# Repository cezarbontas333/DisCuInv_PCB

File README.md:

# DisCuInv_PCB
DisCuInv is an inverter project that aims to implement a simpler power conversion strategy. The aim is to be used in solar to grid conduction, but this is only a prototype used in an educational environment to test different plant control algorithms which may be less computational intensive and less complex to implement, like PIDs or RSTs. It contains a KiCAD project, namely schematic and PCB design, that can be used to create Gerber files, BOM and CPL that can be sent to a manufacturer to create the boards. Additionally, a [proof of concept](https://github.com/cezarbontas333/DisCuInv_PID) program is provided in a separate repository that uses a PID to control the power conversion.

## Highlights
- Features integrated [half-bridge and gate drivers](https://www.infineon.com/cms/en/product/power/motor-control-ics/brushed-dc-motor-control-ics/single-half-bridge-ics/ifx007t/) that can sustain up to 40V DC inputs, but the module designed should use 24V DC.
- Control is done using Infineon's [PSoC C3M5](https://www.infineon.com/cms/en/product/microcontroller/32-bit-psoc-arm-cortex-microcontroller/32-bit-psoc-control-arm-cortex-m33-mcu/psoc-control-c3m/), a modern microcontroller with plenty of features designed for power conversion applications. Pins that are not dedicated to the specific application have been broken out to standard 2.54mm headers for additional expansion modules in testing and prototyping of bonus features.
- Has an integrated power source for the whole logic section of the board. No other power supplies needed, just a IEC C8 socket to be directly plugged.
- Contains on-board LEDs and buttons for testing purposes.

## Disclaimers
This project does not assume any liability or warranty in any state of functioning, including specified or not specified otherwise. The license included covers only the KiCAD project files as described by the schematic and boards design. Other files included as additional resources and dependencies such as component footprints, schematic symbols, datasheets or similar material are subject to their respective owners' licenses and should be treated as such. If any issues appear in this regard, please contact via the platforms issues section or email to the maintainer.

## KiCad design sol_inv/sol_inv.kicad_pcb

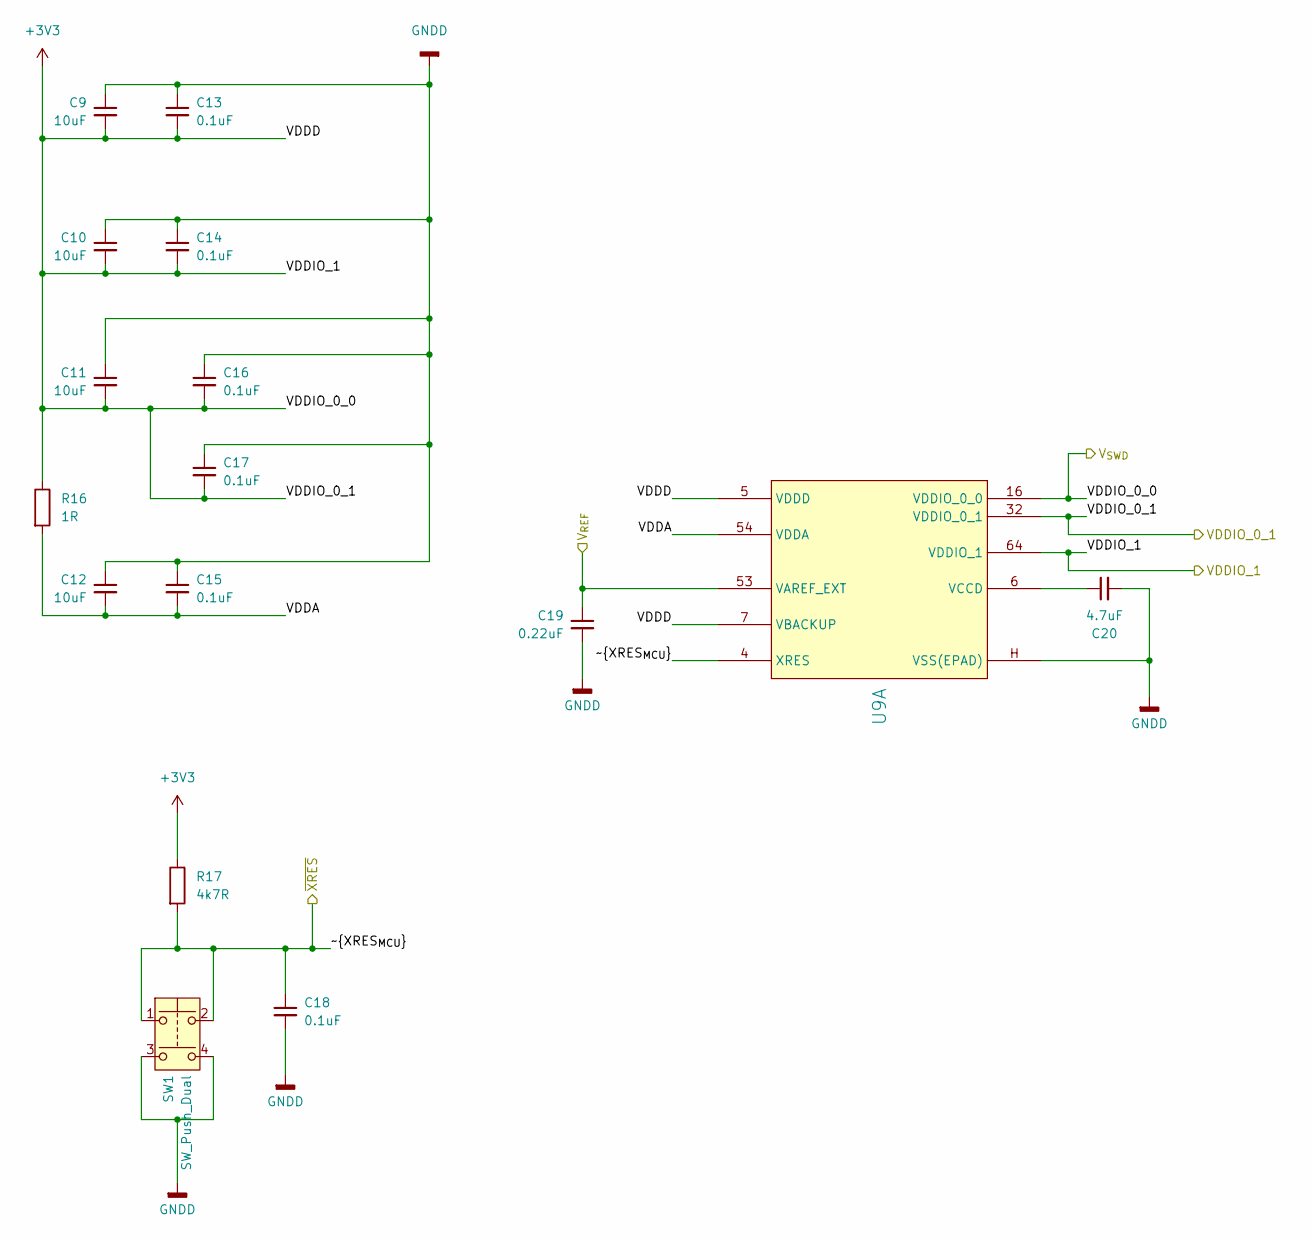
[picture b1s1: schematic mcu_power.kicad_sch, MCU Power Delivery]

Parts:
C9, C10, C11, C12: 10uF; C_0603_1608Metric; Manufacturer Part Number CL10A106KP8NNNC
C13, C14, C15, C16, C17, C18: 0.1uF; C_0402_1005Metric; Manufacturer Part Number C0402C104K4RACTU
C19: 0.22uF; C_0402_1005Metric; Manufacturer Part Number MSASE105SB7224KFNB25
C20: 4.7uF; C_0402_1005Metric; Manufacturer Part Number CC0402KRX5R6BB475
R16: 1R; R_0603_1608Metric; Manufacturer Part Number ERJUP3J1R0V
R17: 4k7R; R_0402_1005Metric; Manufacturer Part Number MCMR04X4701FTL
SW1: SW_Push_Dual; SW_B3F-1000_OMR; Manufacturer Part Number B3F-1000
U9: PSC3M5_E-LQFP-64; LQFP50P1200X1200X160-65N; Manufacturer Part Number PSC3M5FDS2ACQ1XQLA1

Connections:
+3V3: C9.2, C10.2, C11.2, C13.2, C14.2, C16.2, C17.2, R16.1, R17.1, U9.5 (VDDD), U9.7 (VBACKUP), U9.16 (VDDIO_0_0), U9.32 (VDDIO_0_1), U9.64 (VDDIO_1); also elsewhere on the board
/H-Bridge/V_{REF}: C19.1, U9.53 (VAREF_EXT); also elsewhere on the board
/MCU Power/VDDA: C12.2, C15.2, R16.2, U9.54 (VDDA)
/MCU Power/~XRES_{MCU}: C18.1, R17.2, SW1.1, SW1.2, U9.4 (XRES); also elsewhere on the board
GNDD: C9.1, C10.1, C11.1, C12.1, C13.1, C14.1, C15.1, C16.1, C17.1, C18.2, C19.2, C20.2, SW1.3, SW1.4, U9.H (VSS(EPAD)); also elsewhere on the board
unnamed: C20.1, U9.6 (VCCD)

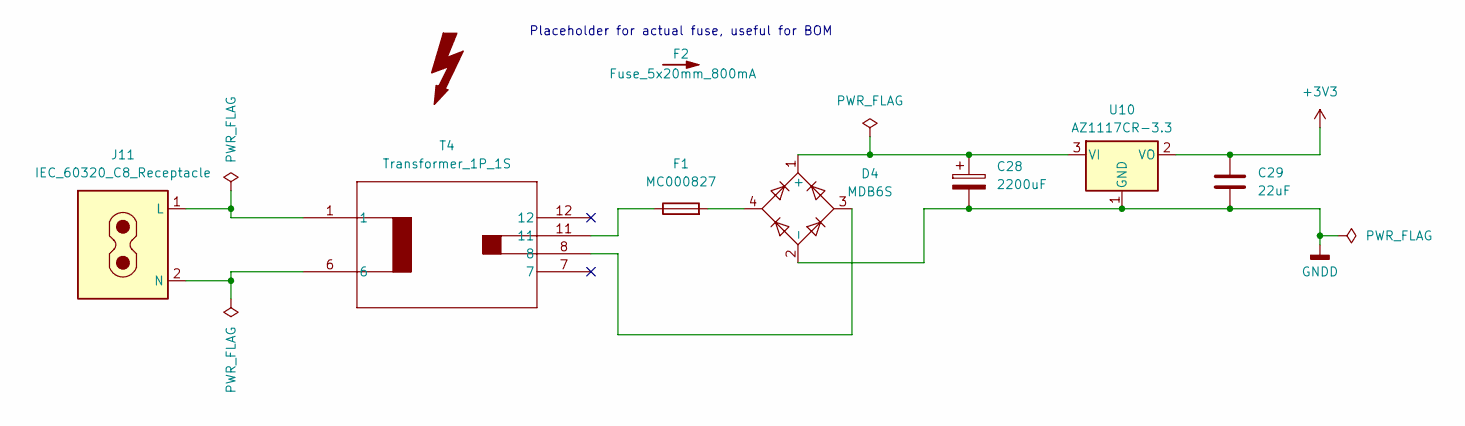
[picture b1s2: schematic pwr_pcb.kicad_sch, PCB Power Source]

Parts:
C28: 2200uF; CP_Radial_D10.0mm_P5.00mm; Manufacturer Part Number 860010275020
C29: 22uF; C_1206_3216Metric; Manufacturer Part Number CC1206KKX5R8BB226
D4: MDB6S; BR_Micro-DIP4_OSI; Manufacturer Part Number MDB6S
F1: MC000827; FUSE_MC000827_MTC; Manufacturer Part Number MC000827
F2: Fuse_5x20mm_800mA; Manufacturer Part Number MP000851
J11: IEC_60320_C8_Receptacle; 43000103; Manufacturer Part Number JR-201S(PCB)
T4: Transformer_1P_1S; 44230_MYR; Manufacturer Part Number 44229
U10: AZ1117CR-3.3; SOT-89-3; Manufacturer Part Number AZ1117CR2-3.3TRG1

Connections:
+3V3: C29.1, U10.2 (VO); also elsewhere on the board
GNDD: C28.2, C29.2, D4.2 (-), U10.1 (GND); also elsewhere on the board
unnamed: C28.1, D4.1 (+), U10.3 (VI)
unnamed: D4.3, T4.8
unnamed: D4.4, F1.2
unnamed: F1.1, T4.11
unnamed: J11.1 (L), T4.1
unnamed: J11.2 (N), T4.6

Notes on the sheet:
Placeholder for actual fuse, useful for BOM

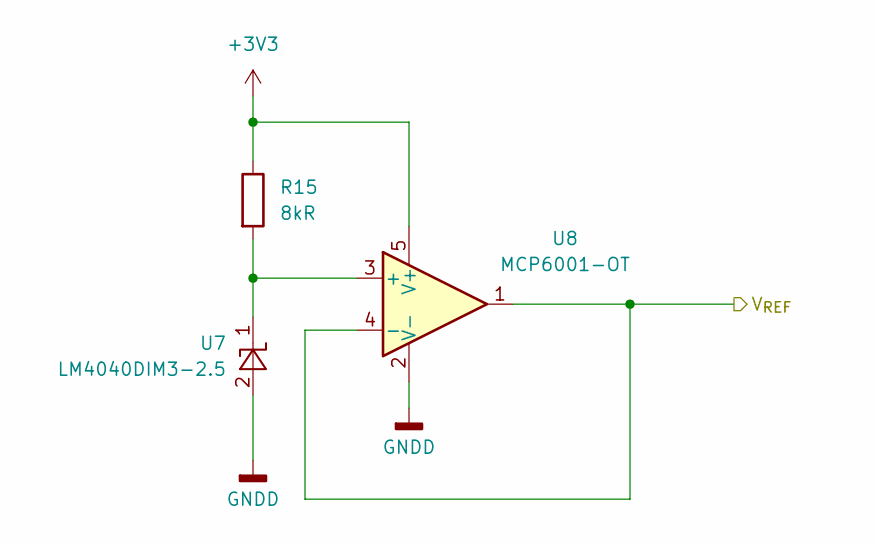
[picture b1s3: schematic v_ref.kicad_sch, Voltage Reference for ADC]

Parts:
R15: 8kR; R_0603_1608Metric; Manufacturer Part Number RT0603BRE078KL
U7: LM4040DIM3-2.5; SOT-23-3; Manufacturer Part Number LM4040DIM3-2.5/NOPB
U8: MCP6001-OT; SOT-23-5; Manufacturer Part Number MCP6001T-I/OT

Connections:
+3V3: R15.1, U8.5 (V+); also elsewhere on the board
/H-Bridge/V_{REF}: U8.1, U8.4 (-); also elsewhere on the board
GNDD: U7.2 (A), U8.2 (V-); also elsewhere on the board
unnamed: R15.2, U7.1 (K), U8.3 (+)

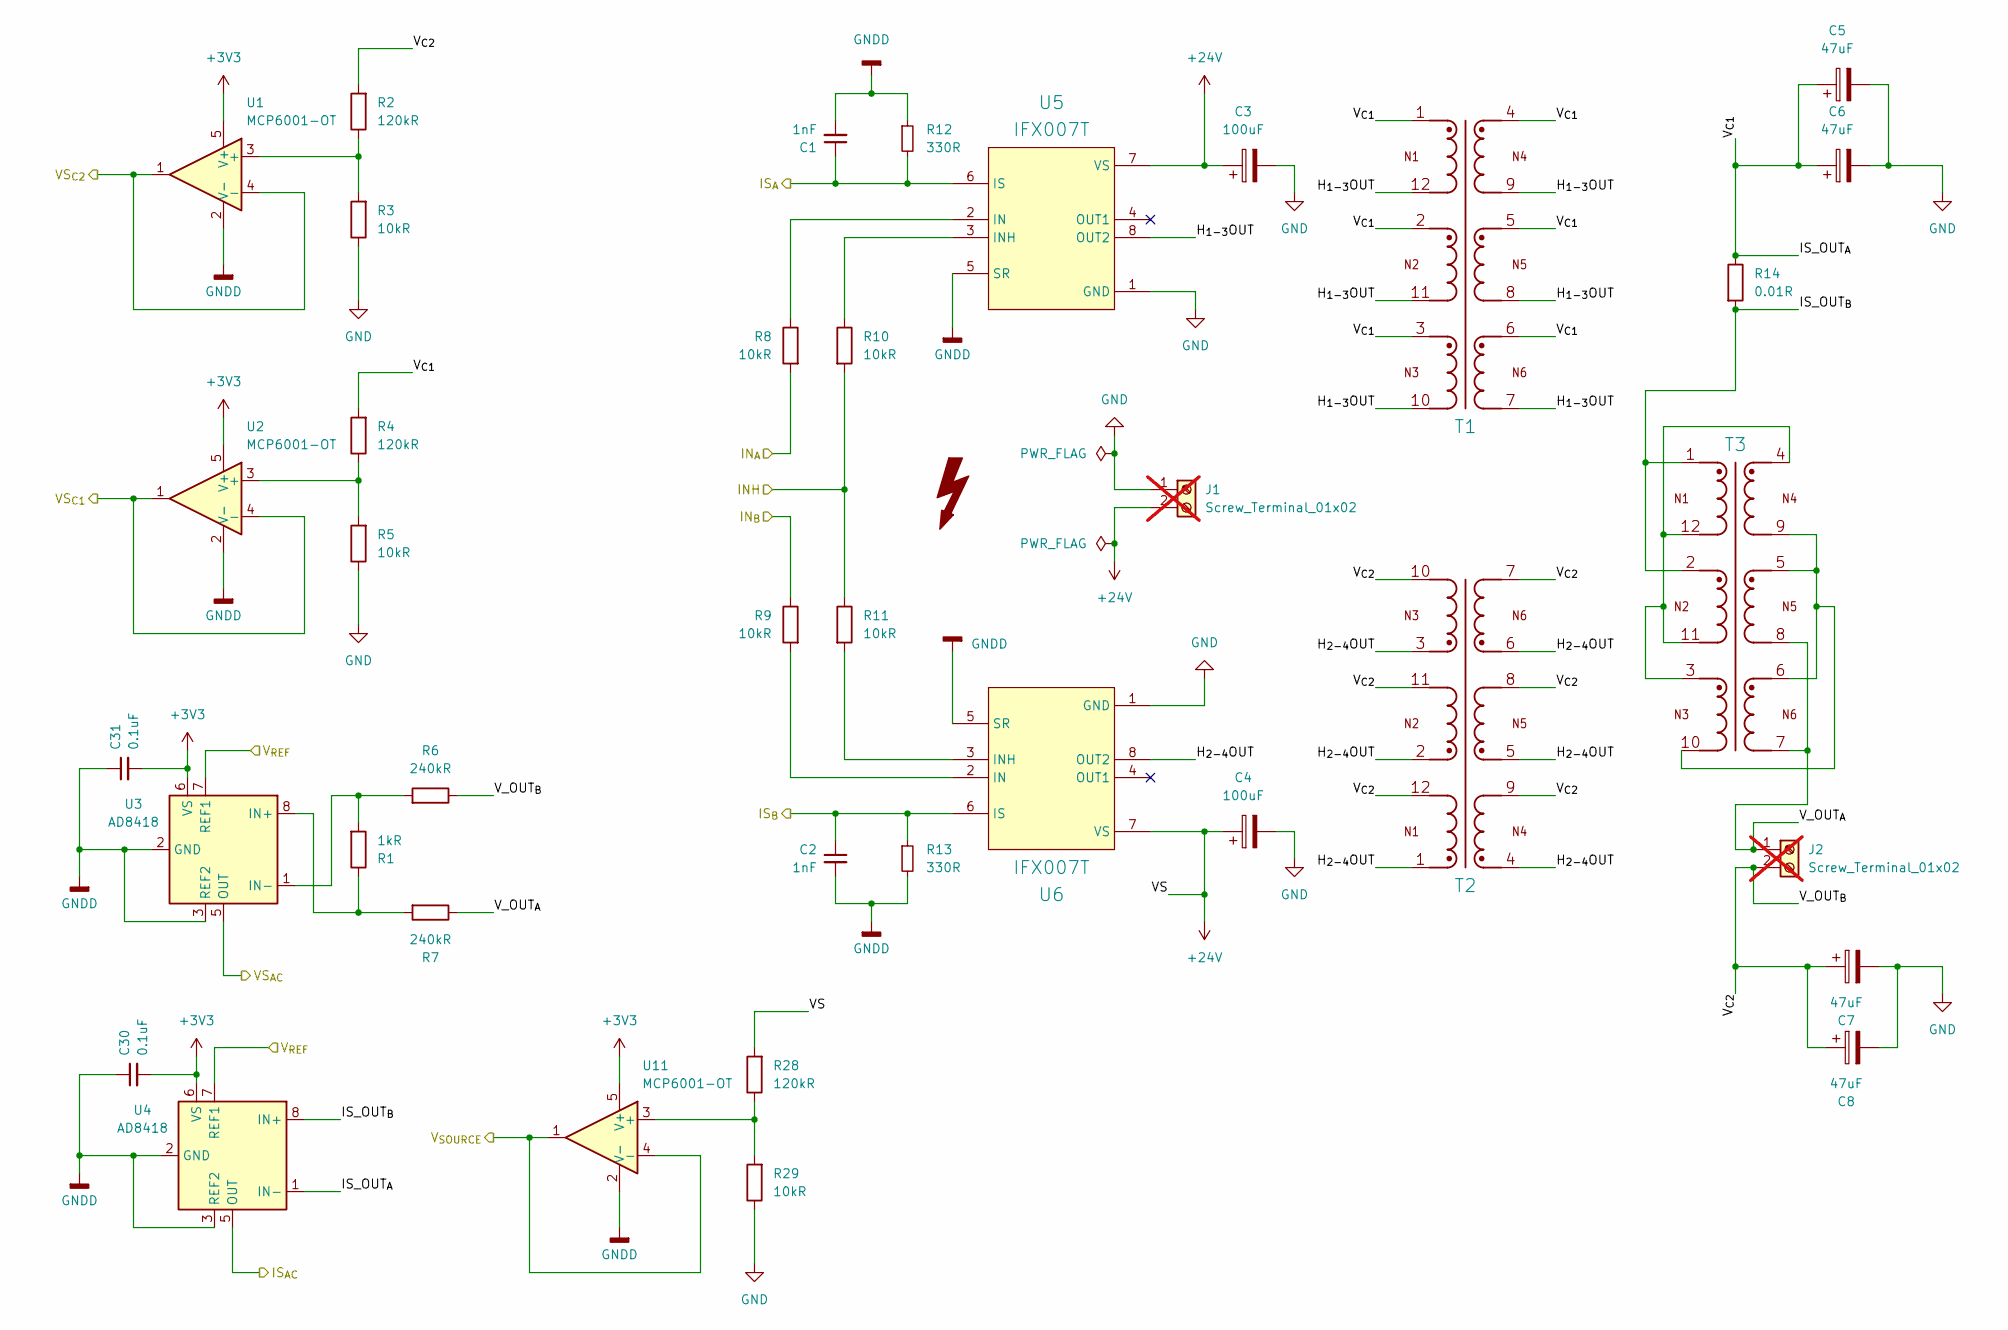
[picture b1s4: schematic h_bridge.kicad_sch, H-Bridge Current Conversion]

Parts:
C1, C2: 1nF; C_0603_1608Metric; Manufacturer Part Number C0603C102K5RECAUTO
C3, C4: 100uF; CP_Elec_8x10; Manufacturer Part Number UUD1H101MNL1GS
C5, C6, C7, C8: 47uF; CP_Elec_8x10; Manufacturer Part Number A785KN476M1JLAS045
C30, C31: 0.1uF; C_0402_1005Metric; Manufacturer Part Number C0402C104K4RACTU
J1, J2: Screw_Terminal_01x02; 691216610002_Handsolder; not fitted
R1: 1kR; R_0805_2012Metric; Manufacturer Part Number MCMR08X1001FTL
R2, R4, R28: 120kR; R_0805_2012Metric; Manufacturer Part Number ERJHP6J124V
R3, R5, R8, R9, R10, R11, R29: 10kR; R_0402_1005Metric; Manufacturer Part Number MR04X1002FTLV
R6, R7: 240kR; R_0603_1608Metric; Manufacturer Part Number ERJ3RED2403V
R12, R13: 330R; R_0603_1608Metric; Manufacturer Part Number CRGCQ0603J330R
R14: 0.01R; R_2512_6332Metric; Manufacturer Part Number WSLP2512R0100FEA
T1, T2, T3: 12uH, 1.7A; WE-FLEX_EFD20; Voltage-µSecond Base 98.4uVs; Manufacturer Part Number 749196521
U1, U2, U11: MCP6001-OT; SOT-23-5; Manufacturer Part Number MCP6001T-I/OT
U3, U4: AD8418; SOIC-8_3.9x4.9mm_P1.27mm; Manufacturer Part Number AD8418AWBRZ-RL
U5, U6: IFX007T; TO127P1500X440-8N-1-V; Manufacturer Part Number IFX007TAUMA1

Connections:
+3V3: C30.2, C31.2, U1.5 (V+), U2.5 (V+), U3.6 (VS), U4.6 (VS), U11.5 (V+); also elsewhere on the board
+24V: C3.1, C4.1, J1.2, R28.2, U5.7 (VS), U6.7 (VS)
/H-Bridge/H_{1-3}OUT: T1.7, T1.8, T1.9, T1.10, T1.11, T1.12, U5.8 (OUT2)
/H-Bridge/H_{2-4}OUT: T2.1, T2.2, T2.3, T2.4, T2.5, T2.6, U6.8 (OUT2)
/H-Bridge/INH: R10.2, R11.1; also elsewhere on the board
/H-Bridge/IN_{A}: R8.2; also elsewhere on the board
/H-Bridge/IN_{B}: R9.1; also elsewhere on the board
/H-Bridge/IS_OUT_{A}: C5.1, C6.1, R4.2, R14.1, T1.1, T1.2, T1.3, T1.4, T1.5, T1.6, U4.1 (IN-)
/H-Bridge/IS_OUT_{B}: R14.2, T3.1, T3.2, U4.8 (IN+)
/H-Bridge/IS_{AC}: U4.5 (OUT); also elsewhere on the board
/H-Bridge/IS_{A}: C1.1, R12.2, U5.6 (IS); also elsewhere on the board
/H-Bridge/IS_{B}: C2.1, R13.1, U6.6 (IS); also elsewhere on the board
/H-Bridge/VS_{AC}: U3.5 (OUT); also elsewhere on the board
/H-Bridge/VS_{C1}: U2.1, U2.4 (-); also elsewhere on the board
/H-Bridge/VS_{C2}: U1.1, U1.4 (-); also elsewhere on the board
/H-Bridge/V_OUT_{A}: J2.1, R7.1, T3.7, T3.8
/H-Bridge/V_OUT_{B}: C7.1, C8.1, J2.2, R2.2, R6.1, T2.7, T2.8, T2.9, T2.10, T2.11, T2.12
/H-Bridge/V_{REF}: U3.7 (REF1), U4.7 (REF1); also elsewhere on the board
/H-Bridge/V_{SOURCE}: U11.1, U11.4 (-); also elsewhere on the board
GND: C3.2, C4.2, C5.2, C6.2, C7.2, C8.2, J1.1, R3.1, R5.1, R29.1, U5.1 (GND), U6.1 (GND)
GNDD: C1.2, C2.2, C30.1, C31.1, R12.1, R13.2, U1.2 (V-), U2.2 (V-), U3.2 (GND), U3.3 (REF2), U4.2 (GND), U4.3 (REF2), U5.5 (SR), U6.5 (SR), U11.2 (V-); also elsewhere on the board
unnamed: T3.5, T3.6, T3.9, T3.10
unnamed: T3.3, T3.4, T3.11, T3.12
unnamed: R2.1, R3.2, U1.3 (+)
unnamed: R4.1, R5.2, U2.3 (+)
unnamed: R1.1, R7.2, U3.8 (IN+)
unnamed: R1.2, R6.2, U3.1 (IN-)
unnamed: R8.1, U5.2 (IN)
unnamed: R10.1, U5.3 (INH)
unnamed: R9.2, U6.2 (IN)
unnamed: R11.2, U6.3 (INH)
unnamed: R28.1, R29.2, U11.3 (+)

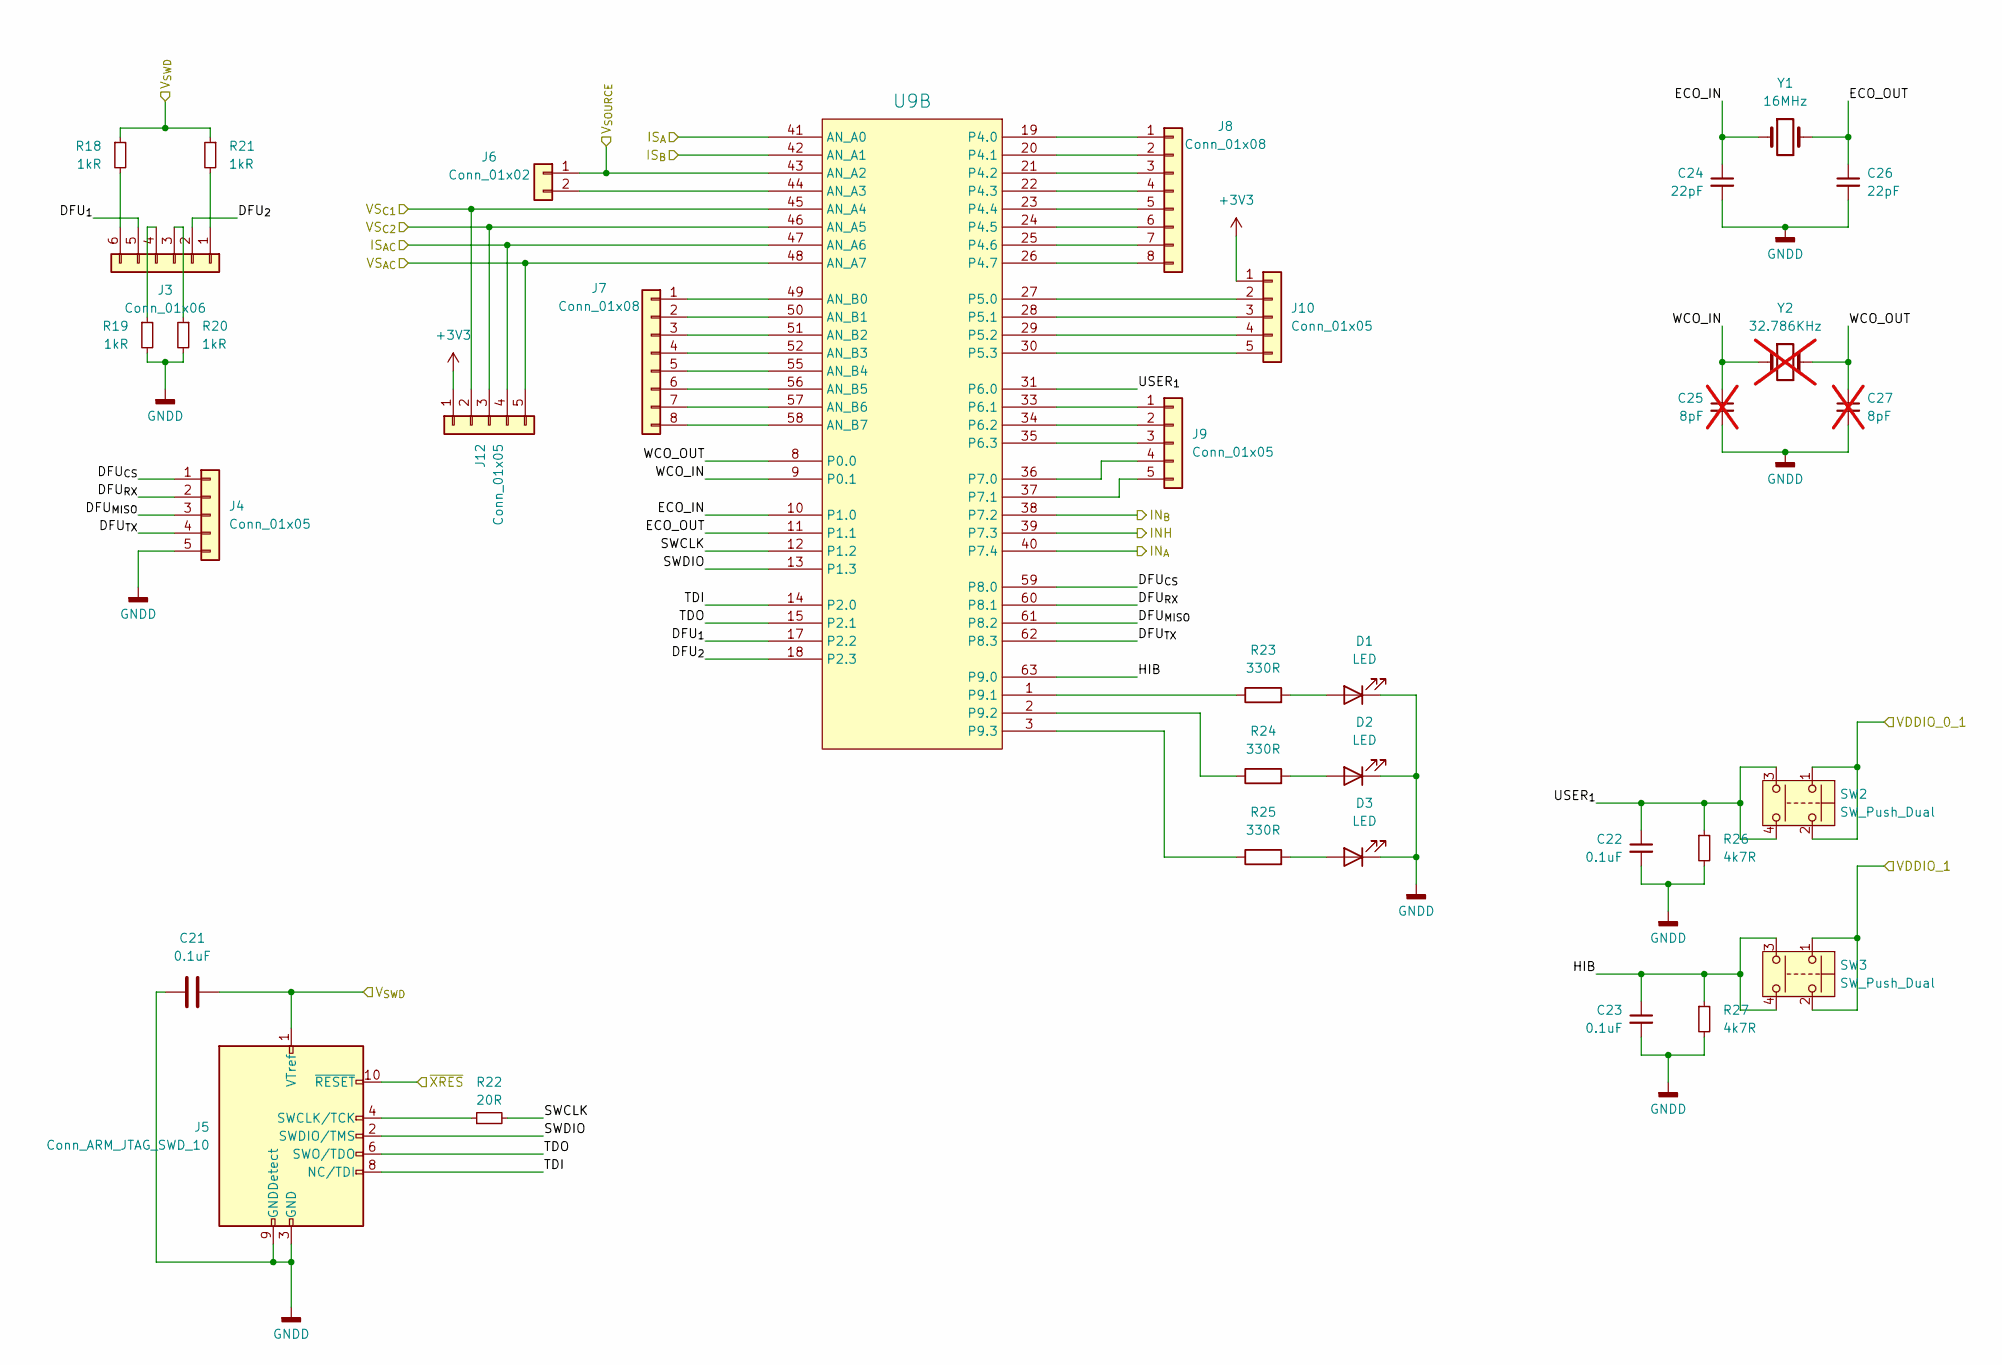
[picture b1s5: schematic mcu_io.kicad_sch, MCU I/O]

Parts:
C21, C22, C23: 0.1uF; C_0402_1005Metric; Manufacturer Part Number C0402C104K4RACTU
C24, C26: 22pF; C_0805_2012Metric; Manufacturer Part Number VJ0805A220GXQCW1BC
C25, C27: 8pF; C_0402_1005Metric; not fitted
D1, D2, D3: LED; LED_0603_1608Metric; Manufacturer Part Number KP-2012SYCK
J3: Conn_01x06; PinHeader_1x06_P2.54mm_Vertical; Manufacturer Part Number TSW-106-07-L-S
J4, J9, J10, J12: Conn_01x05; PinSocket_1x05_P2.54mm_Vertical; Manufacturer Part Number 1593461
J5: Conn_ARM_JTAG_SWD_10; PinHeader_2x05_P1.27mm_Vertical; Manufacturer Part Number 62701021621
J6: Conn_01x02; PinSocket_1x02_P2.54mm_Vertical; Manufacturer Part Number 2212S-02SG-85
J7, J8: Conn_01x08; PinSocket_1x08_P2.54mm_Vertical; Manufacturer Part Number 2212S-08SG-85
R18, R19, R20, R21: 1kR; R_0805_2012Metric; Manufacturer Part Number MCMR08X1001FTL
R22: 20R; R_1206_3216Metric; Manufacturer Part Number MCMR12X20R0FTL
R23, R24, R25: 330R; R_0603_1608Metric; Manufacturer Part Number CRGCQ0603J330R
R26, R27: 4k7R; R_0402_1005Metric; Manufacturer Part Number MCMR04X4701FTL
SW2, SW3: SW_Push_Dual; SW_B3F-1000_OMR; Manufacturer Part Number B3F-1000
U9: PSC3M5_E-LQFP-64; LQFP50P1200X1200X160-65N; Manufacturer Part Number PSC3M5FDS2ACQ1XQLA1
Y1: 16MHz; ABLS7; Manufacturer Part Number ABLS7M2-16.000MHZ-D-2Y-T
Y2: 32.786KHz; Crystal_DS26_D2.0mm_L6.0mm_Vertical; not fitted

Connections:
+3V3: C21.1, J5.1 (VTref), J10.1, J12.1, R18.1, R21.1, SW2.1, SW2.2, SW3.1, SW3.2; also elsewhere on the board
/H-Bridge/INH: U9.39 (P7.3); also elsewhere on the board
/H-Bridge/IN_{A}: U9.40 (P7.4); also elsewhere on the board
/H-Bridge/IN_{B}: U9.38 (P7.2); also elsewhere on the board
/H-Bridge/IS_{AC}: J12.4, U9.47 (AN_A6); also elsewhere on the board
/H-Bridge/IS_{A}: U9.41 (AN_A0); also elsewhere on the board
/H-Bridge/IS_{B}: U9.42 (AN_A1); also elsewhere on the board
/H-Bridge/VS_{AC}: J12.5, U9.48 (AN_A7); also elsewhere on the board
/H-Bridge/VS_{C1}: J12.2, U9.45 (AN_A4); also elsewhere on the board
/H-Bridge/VS_{C2}: J12.3, U9.46 (AN_A5); also elsewhere on the board
/H-Bridge/V_{SOURCE}: J6.1, U9.43 (AN_A2); also elsewhere on the board
/MCU IO/DFU_{1}: J3.5, U9.17 (P2.2)
/MCU IO/DFU_{2}: J3.2, U9.18 (P2.3)
/MCU IO/DFU_{CS}: J4.1, U9.59 (P8.0)
/MCU IO/DFU_{MISO}: J4.3, U9.61 (P8.2)
/MCU IO/DFU_{RX}: J4.2, U9.60 (P8.1)
/MCU IO/DFU_{TX}: J4.4, U9.62 (P8.3)
/MCU IO/ECO_IN: C24.1, U9.10 (P1.0), Y1.1
/MCU IO/ECO_OUT: C26.1, U9.11 (P1.1), Y1.2
/MCU IO/HIB: C23.1, R27.1, SW3.3, SW3.4, U9.63 (P9.0)
/MCU IO/SWCLK: R22.2, U9.12 (P1.2)
/MCU IO/SWDIO: J5.2 (SWDIO/TMS), U9.13 (P1.3)
/MCU IO/TDI: J5.8 (NC/TDI), U9.14 (P2.0)
/MCU IO/TDO: J5.6 (SWO/TDO), U9.15 (P2.1)
/MCU IO/USER_{1}: C22.1, R26.1, SW2.3, SW2.4, U9.31 (P6.0)
/MCU IO/WCO_IN: C25.1, U9.9 (P0.1), Y2.1
/MCU IO/WCO_OUT: C27.1, U9.8 (P0.0), Y2.2
/MCU Power/~XRES_{MCU}: J5.10 (~RESET); also elsewhere on the board
GNDD: C21.2, C22.2, C23.2, C24.2, C25.2, C26.2, C27.2, D1.1 (K), D2.1 (K), D3.1 (K), J4.5, J5.3 (GND), J5.5 (GND), J5.9 (GNDDetect), R19.2, R20.2, R26.2, R27.2; also elsewhere on the board
unnamed: D1.2 (A), R23.2
unnamed: D2.2 (A), R24.2
unnamed: D3.2 (A), R25.2
unnamed: J3.1, R21.2
unnamed: J3.3, R20.1
unnamed: J3.4, R19.1
unnamed: J3.6, R18.2
unnamed: J5.4 (SWCLK/TCK), R22.1
unnamed: J6.2, U9.44 (AN_A3)
unnamed: J7.1, U9.49 (AN_B0)
unnamed: J7.2, U9.50 (AN_B1)
unnamed: J7.3, U9.51 (AN_B2)
unnamed: J7.4, U9.52 (AN_B3)
unnamed: J7.5, U9.55 (AN_B4)
unnamed: J7.6, U9.56 (AN_B5)
unnamed: J7.7, U9.57 (AN_B6)
unnamed: J7.8, U9.58 (AN_B7)
unnamed: J8.1, U9.19 (P4.0)
unnamed: J8.2, U9.20 (P4.1)
unnamed: J8.3, U9.21 (P4.2)
unnamed: J8.4, U9.22 (P4.3)
unnamed: J8.5, U9.23 (P4.4)
unnamed: J8.6, U9.24 (P4.5)
unnamed: J8.7, U9.25 (P4.6)
unnamed: J8.8, U9.26 (P4.7)
unnamed: J9.1, U9.33 (P6.1)
unnamed: J9.2, U9.34 (P6.2)
unnamed: J9.3, U9.35 (P6.3)
unnamed: J9.4, U9.36 (P7.0)
unnamed: J9.5, U9.37 (P7.1)
unnamed: J10.2, U9.27 (P5.0)
unnamed: J10.3, U9.28 (P5.1)
unnamed: J10.4, U9.29 (P5.2)
unnamed: J10.5, U9.30 (P5.3)
unnamed: R23.1, U9.1 (P9.1)
unnamed: R24.1, U9.2 (P9.2)
unnamed: R25.1, U9.3 (P9.3)

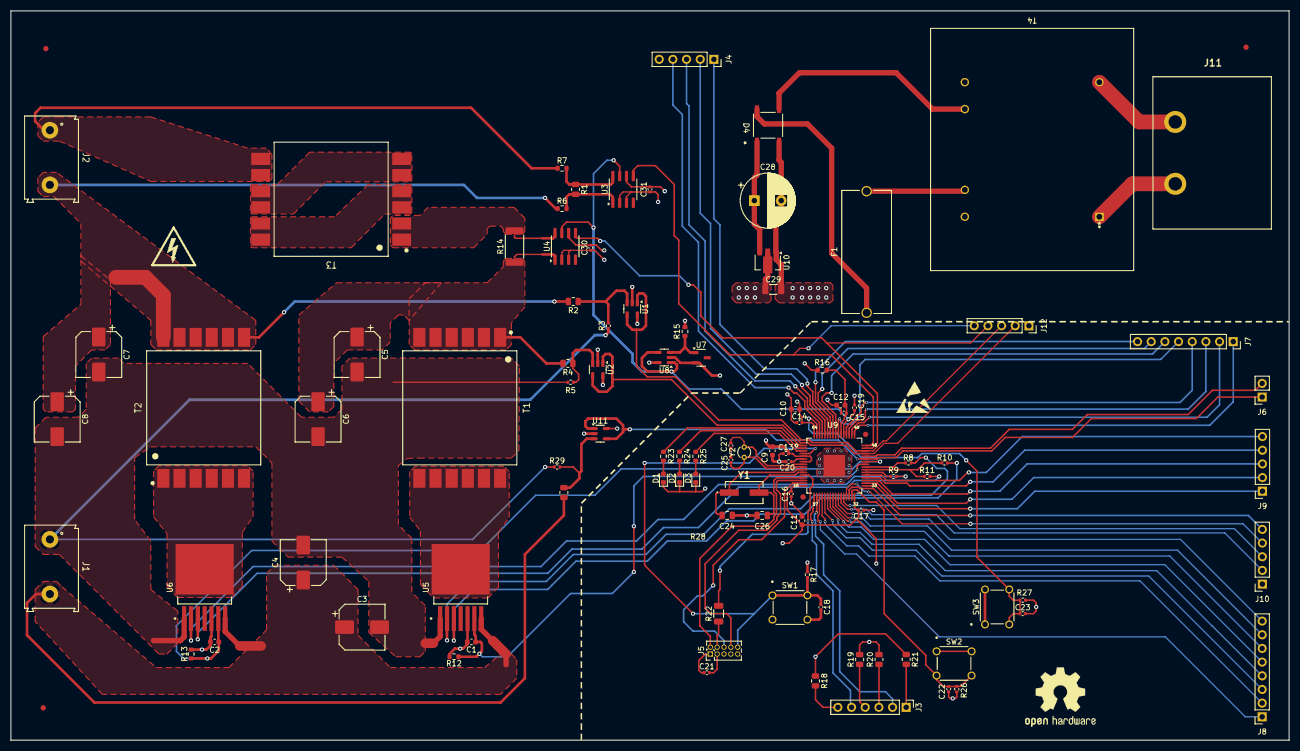
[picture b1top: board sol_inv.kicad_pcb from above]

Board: 4 copper layers, 237.5 x 135.5 mm, 100 parts (0 on the bottom side), 95 nets.

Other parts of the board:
FID1**, FID2**, FID3**: Fiducial_1mm_Mask2mm

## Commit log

2025-04-09 0.1v full schematic done
2025-04-22 v0.2 components change + reference to providers
2025-04-24 initial component placement
2025-05-05 v0.3 pcb layout pre-drc fixes
2025-05-08 v0.3.1 drc fixes + layout tweaks
2025-05-09 v0.3.2 hbridge plane tweaks
2025-05-12 Actual README file
2025-05-12 Updated to proper hardware related FOSHW license
2025-05-12 Corrected typos
2025-05-27 v0.3.4 fixes + component change for farnell
2025-07-29 v0.4 fixed mcu ldo part, production testing
2025-07-29 Update LICENSE to OSHW
2025-07-29 Restore Readme
